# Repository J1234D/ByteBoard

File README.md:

# ByteBoard

ByteBoard is my custom 3×3 mechanical macropad powered by the Seeed Studio XIAO RP2040. It has 9 programmable mechanical keys, a rotary encoder, a 0.91" OLED display, per-key RGB lighting, and a custom PCB and 3D-printed case that I designed from scratch.

I started this project as part of Hack Club Stardance because I wanted to learn PCB design, CAD, and keyboard firmware by building something I would actually use. Instead of modifying an existing design, I challenged myself to design everything—from the schematic and PCB to the enclosure and firmware.

The result is a compact macropad that's useful for coding, video editing, media controls, and everyday shortcuts while also being a fun project to customize. Since everything is open source, you can easily change the firmware, modify the hardware, or even design your own version.

➡️ [Read the full journal](./JOURNAL.md)

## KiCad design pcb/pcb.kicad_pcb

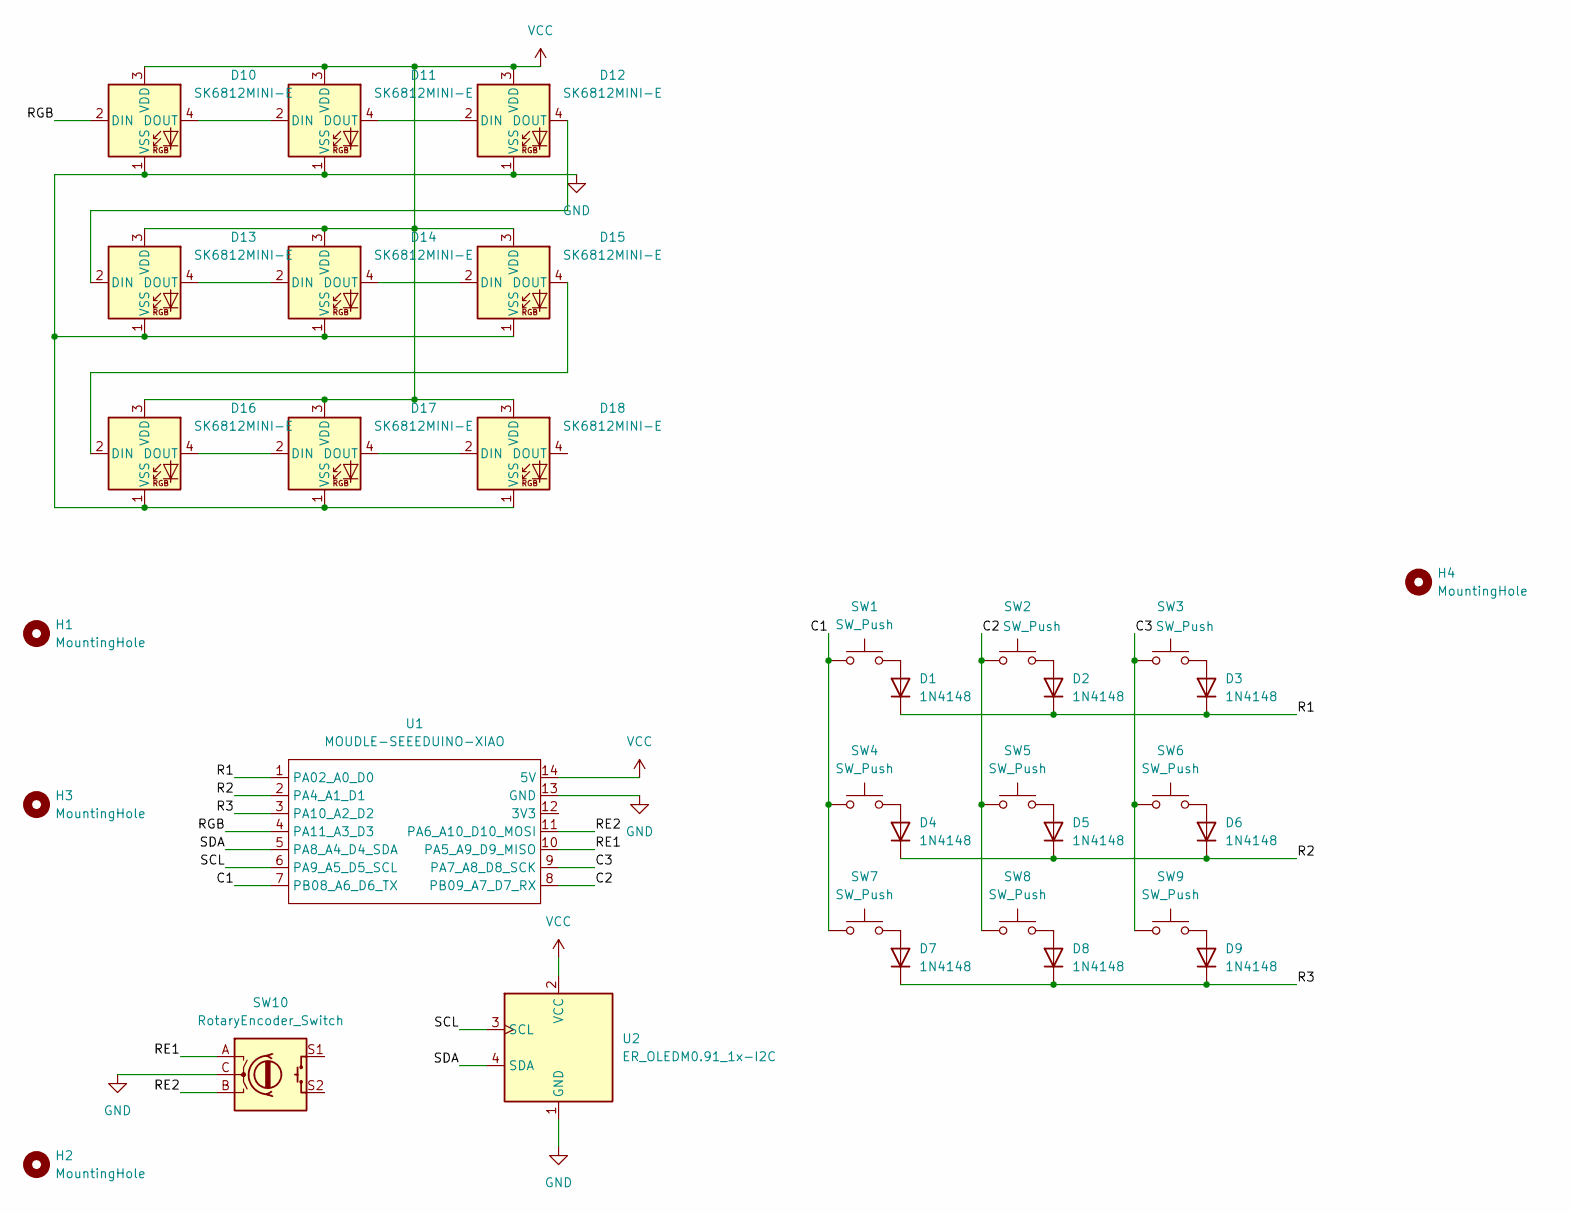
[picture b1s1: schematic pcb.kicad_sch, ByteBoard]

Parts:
D1, D2, D3, D4, D5, D6, D7, D8, D9: 1N4148; D_DO-35_SOD27_P7.62mm_Horizontal
D10, D11, D12, D13, D14, D15, D16, D17, D18: SK6812MINI-E; LED_SK6812MINI-E_3.2x2.8mm_P1.5mm_ReverseMount
H1, H2, H3, H4: MountingHole; MountingHole_3.2mm_M3
SW1, SW2, SW3, SW4, SW5, SW6, SW7, SW8, SW9: SW_Push; SW_Cherry_MX_1.00u_PCB_Custom
SW10: RotaryEncoder_Switch; RotaryEncoder_Alps_EC11E-Switch_Vertical_H20mm
U1: MOUDLE-SEEEDUINO-XIAO; XIAO-Generic-Hybrid-14P-2.54-21X17.8MM
U2: ER_OLEDM0.91_1x-I2C

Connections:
/C1: SW1.1, SW4.1, SW7.1, U1.7 (PB08_A6_D6_TX)
/C2: SW2.1, SW5.1, SW8.1, U1.8 (PB09_A7_D7_RX)
/C3: SW3.1, SW6.1, SW9.1, U1.9 (PA7_A8_D8_SCK)
/R1: D1.1 (K), D2.1 (K), D3.1 (K), U1.1 (PA02_A0_D0)
/R2: D4.1 (K), D5.1 (K), D6.1 (K), U1.2 (PA4_A1_D1)
/R3: D7.1 (K), D8.1 (K), D9.1 (K), U1.3 (PA10_A2_D2)
/RE1: SW10.A, U1.10 (PA5_A9_D9_MISO)
/RE2: SW10.B, U1.11 (PA6_A10_D10_MOSI)
/RGB: D10.2 (DIN), U1.4 (PA11_A3_D3)
/SCL: U1.6 (PA9_A5_D5_SCL), U2.3 (SCL)
/SDA: U1.5 (PA8_A4_D4_SDA), U2.4 (SDA)
GND: D10.1 (VSS), D11.1 (VSS), D12.1 (VSS), D13.1 (VSS), D14.1 (VSS), D15.1 (VSS), D16.1 (VSS), D17.1 (VSS), D18.1 (VSS), SW10.C, U1.13 (GND), U2.1 (GND)
unnamed: D1.2 (A), SW1.2
unnamed: D2.2 (A), SW2.2
unnamed: D3.2 (A), SW3.2
unnamed: D4.2 (A), SW4.2
unnamed: D5.2 (A), SW5.2
unnamed: D6.2 (A), SW6.2
unnamed: D7.2 (A), SW7.2
unnamed: D8.2 (A), SW8.2
unnamed: D9.2 (A), SW9.2
unnamed: D10.4 (DOUT), D11.2 (DIN)
unnamed: D11.4 (DOUT), D12.2 (DIN)
unnamed: D12.4 (DOUT), D13.2 (DIN)
unnamed: D13.4 (DOUT), D14.2 (DIN)
unnamed: D14.4 (DOUT), D15.2 (DIN)
unnamed: D15.4 (DOUT), D16.2 (DIN)
unnamed: D16.4 (DOUT), D17.2 (DIN)
unnamed: D17.4 (DOUT), D18.2 (DIN)
VCC: D10.3 (VDD), D11.3 (VDD), D12.3 (VDD), D13.3 (VDD), D14.3 (VDD), D15.3 (VDD), D16.3 (VDD), D17.3 (VDD), D18.3 (VDD), U1.14 (5V), U2.2 (VCC)

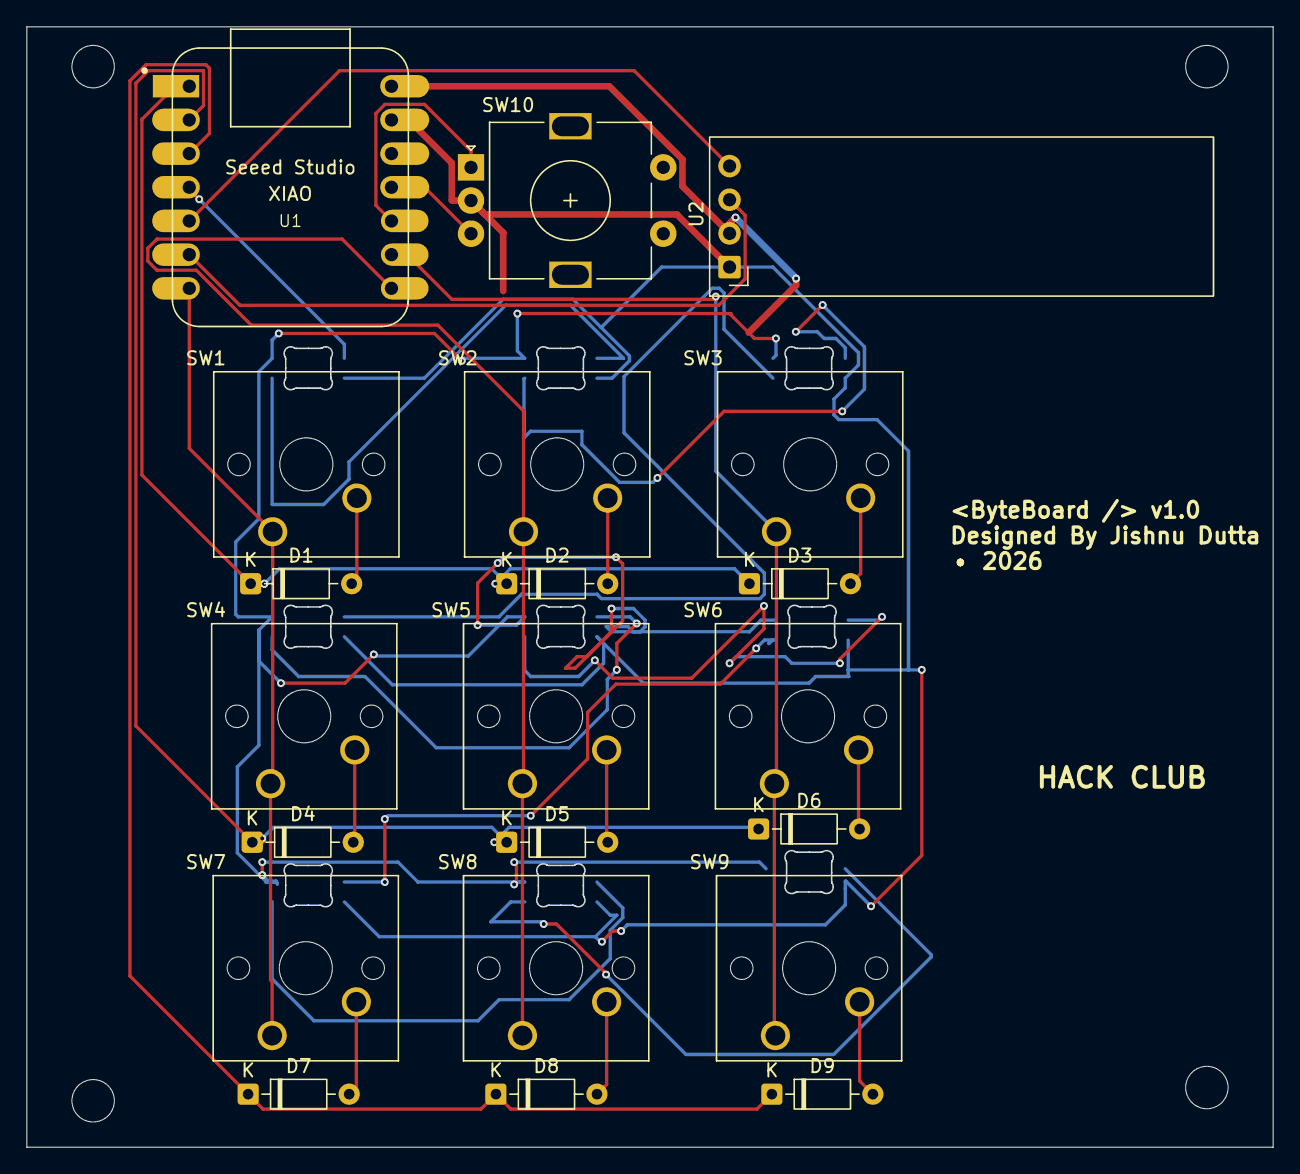
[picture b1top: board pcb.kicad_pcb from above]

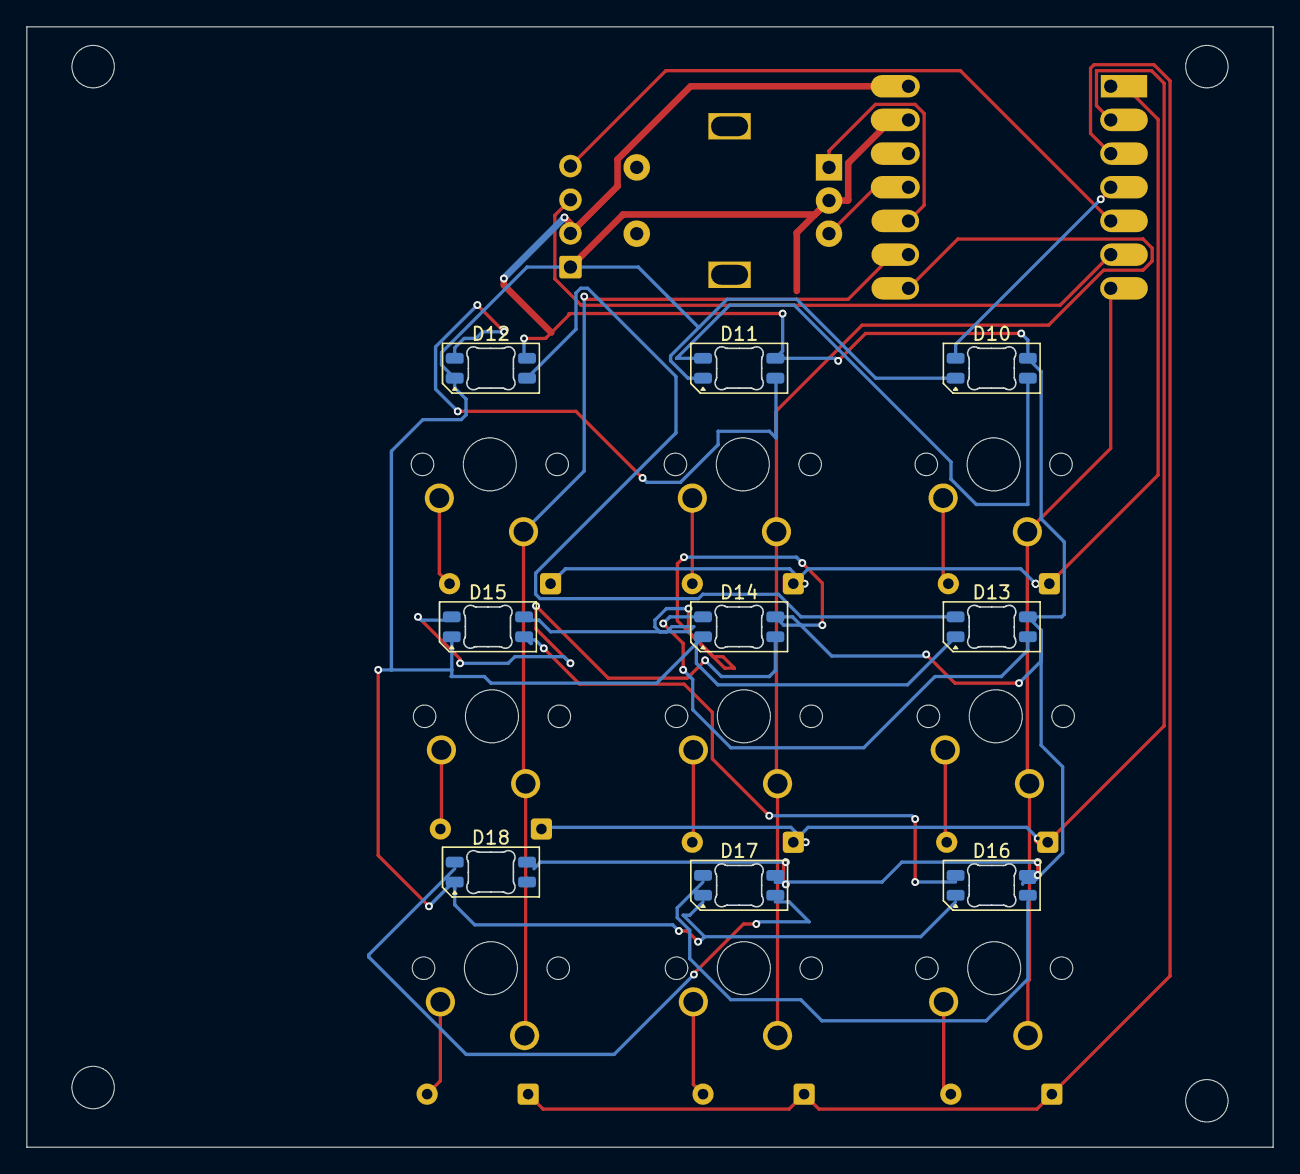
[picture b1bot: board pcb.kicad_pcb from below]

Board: 2 copper layers, 94.0 x 84.5 mm, 34 parts (9 on the bottom side), 30 nets.

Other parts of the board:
H3#2: MountingHole; MountingHole_3.2mm_M3

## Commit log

2026-06-20 making the schematic
2026-06-21 making the schematic and adding assets
2026-06-21 routing on the pcb
2026-06-22 add readme and logo
2026-06-22 added journal and removed readme
2026-06-23 update Journal
2026-06-23 Rename Journal.md to JOURNAL.md
2026-06-23 Add latest progress section to README
2026-06-25 fixed silkscreen
2026-06-28 updated journal
2026-06-28 Update JOURNAL and add firmware
2026-06-28 added CAD files
2026-06-28 added BOM.csv
2026-06-28 update BOM
2026-06-28 updated BOM
